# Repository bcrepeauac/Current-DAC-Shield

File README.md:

# Current-DAC-Shield
Current D-A Shield for Arduino

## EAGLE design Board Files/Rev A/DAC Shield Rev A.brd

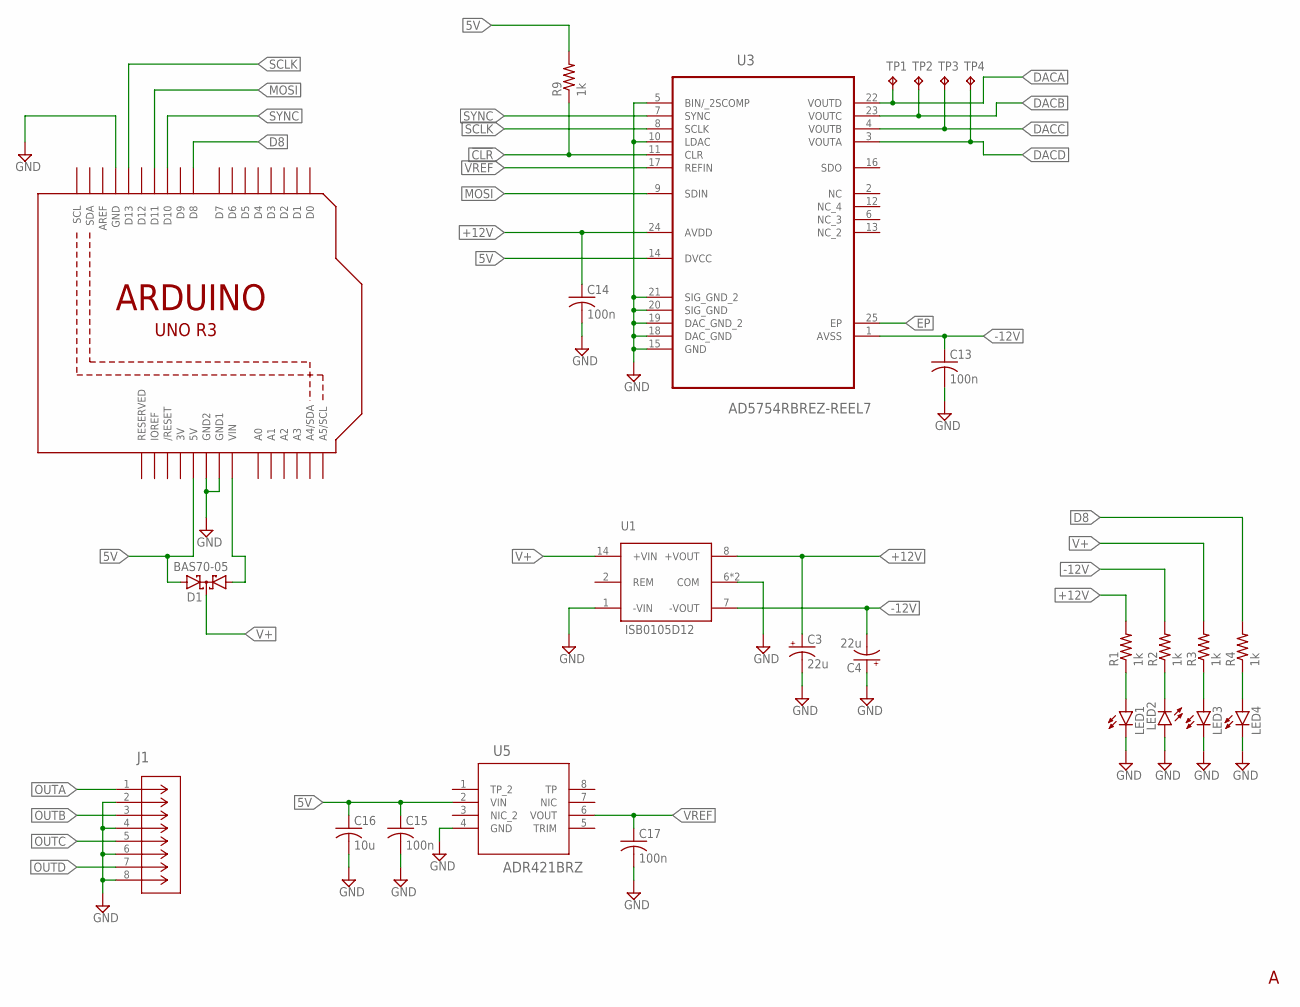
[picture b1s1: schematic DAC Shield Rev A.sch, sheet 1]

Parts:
C3, C4: 22u; C/6032-28W
C13, C14, C15, C17: 100n; C0805
C16: 10u; C0805
D1: BAS70-05; SOT23
J1: OSTVN08A150; CONN_OSTVN08A150_OST
LED1, LED2, LED3, LED4: LEDCHIPLED_0805; CHIPLED_0805
R1, R2, R3, R4, R9: 1k; R0805
TP1, TP2, TP3, TP4: TPB1,27; B1,27
U1: ISB0105D12; SOP254P1860X845-14L
U2: ARDUINOR3-BPLACE
U3: AD5754RBREZ-REEL7; SOP65P640X120-25N
U5: ADR421BRZ; R_8_ADI

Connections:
3V: U2.3V
5V: C15.1, C16.1, D1.2 (A2), R9.2, U2.5V, U3.14 (DVCC), U5.2 (VIN)
!CLR: R9.1, U3.11 (CLR)
+12V: C3.+, C14.1, R1.2, U1.8 (+VOUT), U3.24 (AVDD); also elsewhere on the board
-12V: C4.-, C13.1, R2.2, U1.7 (-VOUT), U3.1 (AVSS); also elsewhere on the board
D8: R4.2, U2.D8
DACA: TP1.TP, U3.22 (VOUTD); also elsewhere on the board
DACB: TP2.TP, U3.23 (VOUTC); also elsewhere on the board
DACC: TP3.TP, U3.4 (VOUTB); also elsewhere on the board
DACD: TP4.TP, U3.3 (VOUTA); also elsewhere on the board
EP: U3.25 (EP)
GND: C3.-, C4.+, C13.2, C14.2, C15.2, C16.2, C17.2, J1.2, J1.4, J1.6, J1.8, LED1.C, LED2.A, LED3.C, LED4.C, U1.1 (-VIN), U1.6 (COM), U1.9 (COM), U2.GND, U2.GND1, U2.GND2, U3.5 (BIN/_2SCOMP), U3.10 (LDAC), U3.15 (GND), U3.18 (DAC_GND), U3.19 (DAC_GND_2), U3.20 (SIG_GND), U3.21 (SIG_GND_2), U5.4 (GND); also elsewhere on the board
MOSI: U2.D11, U3.9 (SDIN)
unnamed: D1.1 (A1), U2.VIN
unnamed: LED1.A, R1.1
unnamed: LED2.C, R2.1
unnamed: LED3.A, R3.1
unnamed: LED4.A, R4.1
OUTA: J1.1; also elsewhere on the board
OUTB: J1.3; also elsewhere on the board
OUTC: J1.5; also elsewhere on the board
OUTD: J1.7; also elsewhere on the board
SCLK: U2.D13, U3.8 (SCLK)
SYNC: U2.D10, U3.7 (SYNC)
V+: D1.3 (C), R3.2, U1.14 (+VIN)
VREF: C17.1, U3.17 (REFIN), U5.6 (VOUT)

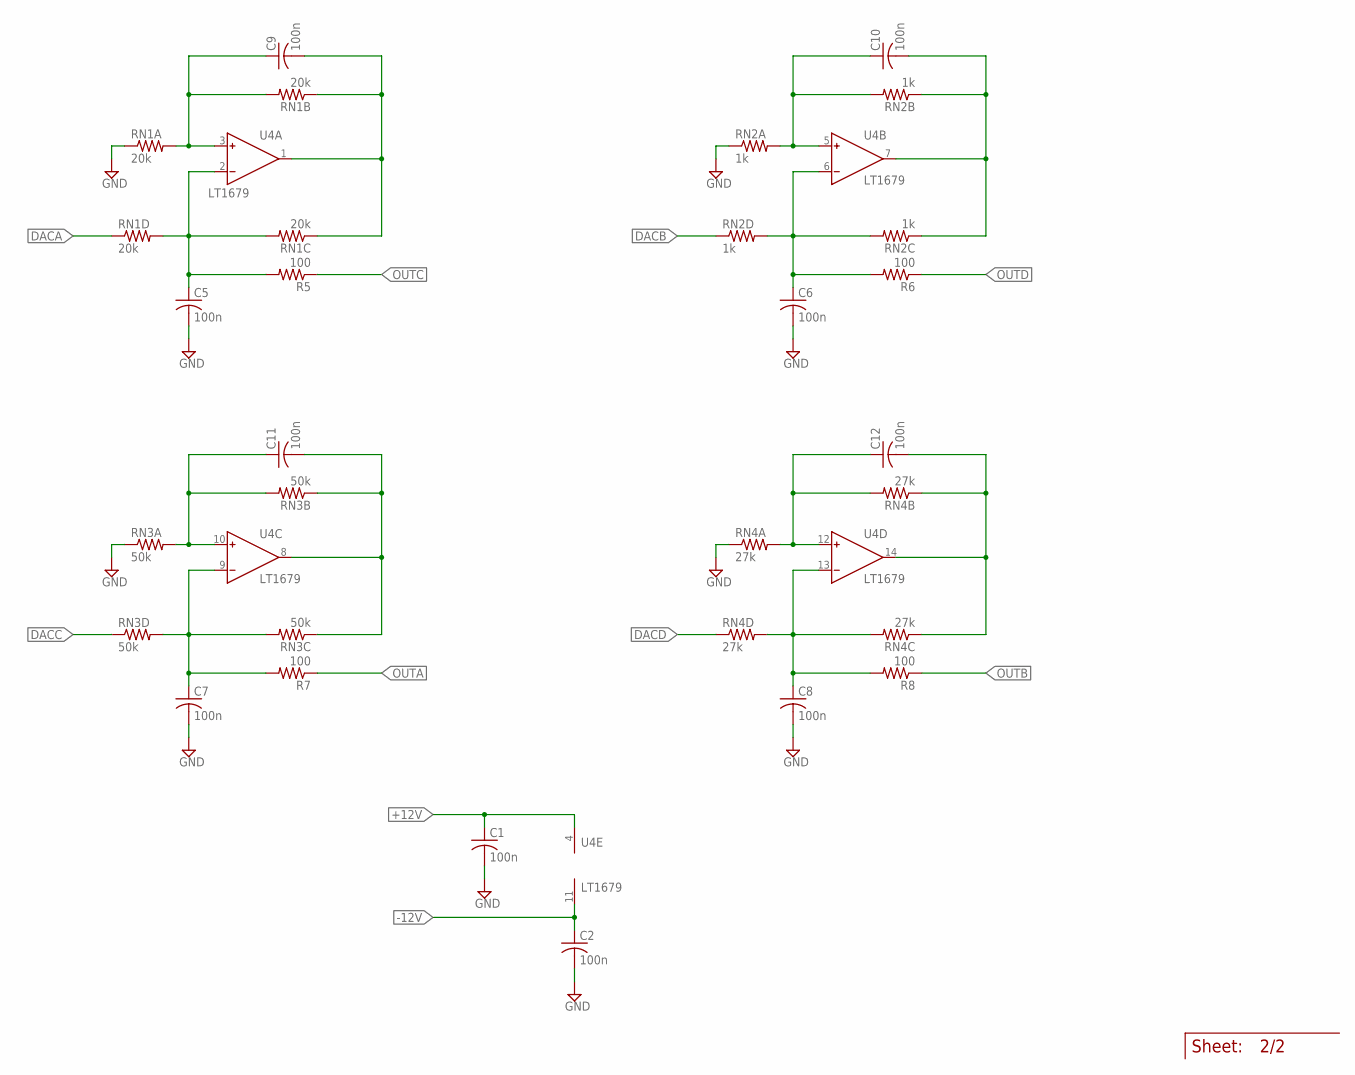
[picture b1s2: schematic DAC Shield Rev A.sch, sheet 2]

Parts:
C1, C2, C5, C6, C7, C8, C9, C10, C11, C12: 100n; C0805
R5, R6, R7, R8: 100; R0805
RN1: 20k; RESCAV80P320X150X55-8N
RN2: 1k; RESCAV80P320X150X55-8N
RN3: 50k; RESCAV80P320X150X55-8N
RN4: 27k; RESCAV80P320X150X55-8N
U4: LT1679; R_14_ADI-M

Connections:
+12V: C1.1, U4.4 (V+); also elsewhere on the board
-12V: C2.1, U4.11 (V-); also elsewhere on the board
DACA: RN1.4 (1); also elsewhere on the board
DACB: RN2.4 (1); also elsewhere on the board
DACC: RN3.4 (1); also elsewhere on the board
DACD: RN4.4 (1); also elsewhere on the board
GND: C1.2, C2.2, C5.2, C6.2, C7.2, C8.2, RN1.1, RN2.1, RN3.1, RN4.1; also elsewhere on the board
unnamed: C10.1, RN2.7 (2), RN2.8 (2), U4.5 (IN+)
unnamed: C9.1, RN1.7 (2), RN1.8 (2), U4.3 (IN+)
unnamed: C9.2, RN1.2 (1), RN1.3 (1), U4.1 (OUT)
unnamed: C10.2, RN2.2 (1), RN2.3 (1), U4.7 (OUT)
unnamed: C11.1, RN3.7 (2), RN3.8 (2), U4.10 (IN+)
unnamed: C11.2, RN3.2 (1), RN3.3 (1), U4.8 (OUT)
unnamed: C12.1, RN4.7 (2), RN4.8 (2), U4.12 (IN+)
unnamed: C12.2, RN4.2 (1), RN4.3 (1), U4.14 (OUT)
unnamed: C5.1, R5.2, RN1.5 (2), RN1.6 (2), U4.2 (IN-)
unnamed: C6.1, R6.2, RN2.5 (2), RN2.6 (2), U4.6 (IN-)
unnamed: C7.1, R7.2, RN3.5 (2), RN3.6 (2), U4.9 (IN-)
unnamed: C8.1, R8.2, RN4.5 (2), RN4.6 (2), U4.13 (IN-)
OUTA: R7.1; also elsewhere on the board
OUTB: R8.1; also elsewhere on the board
OUTC: R5.1; also elsewhere on the board
OUTD: R6.1; also elsewhere on the board

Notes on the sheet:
Sheet:

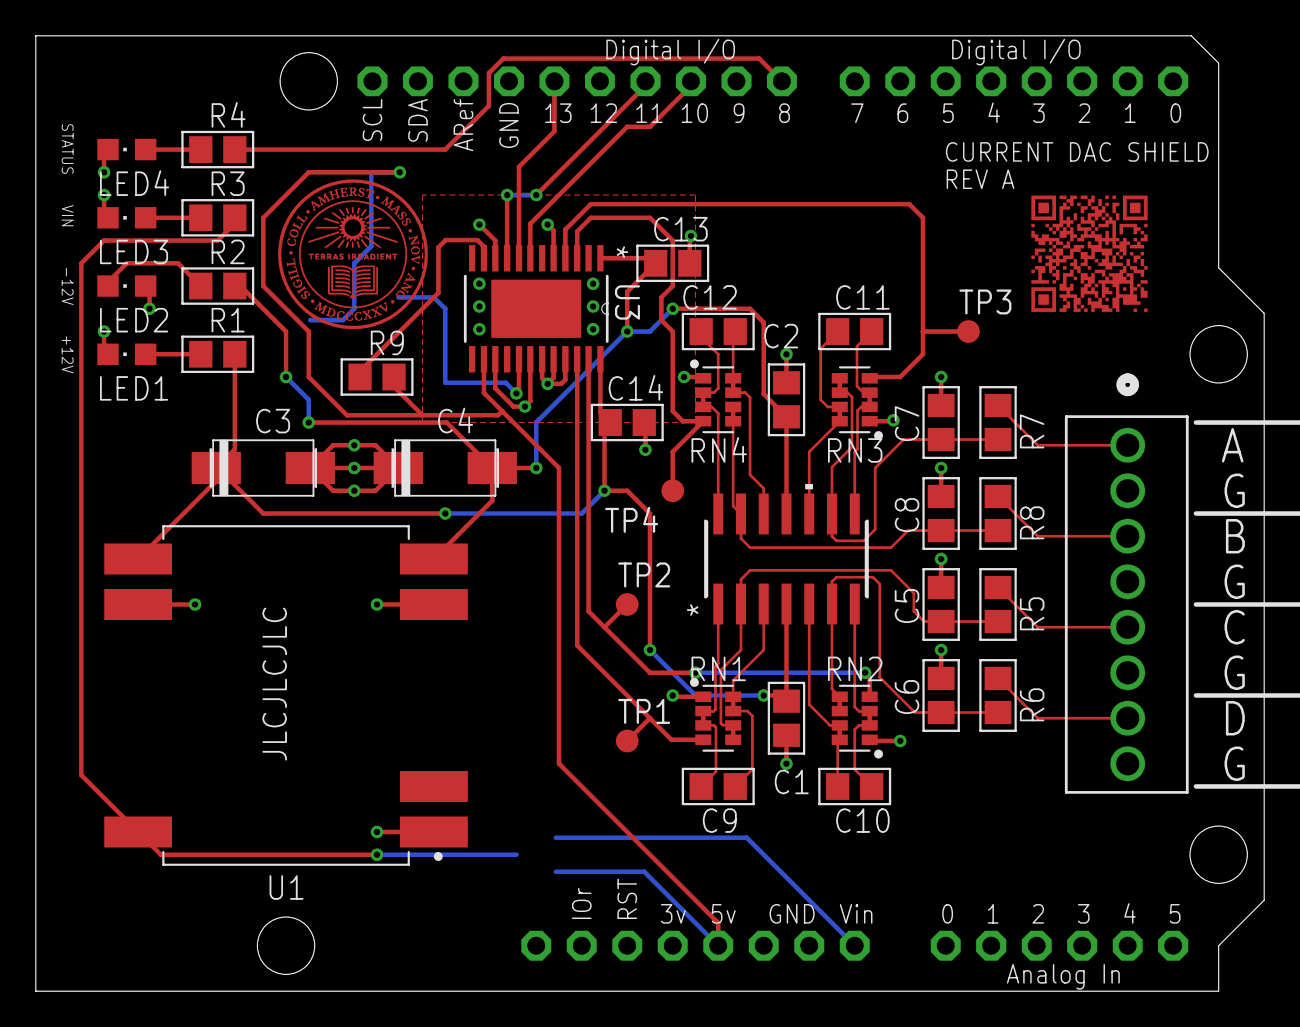
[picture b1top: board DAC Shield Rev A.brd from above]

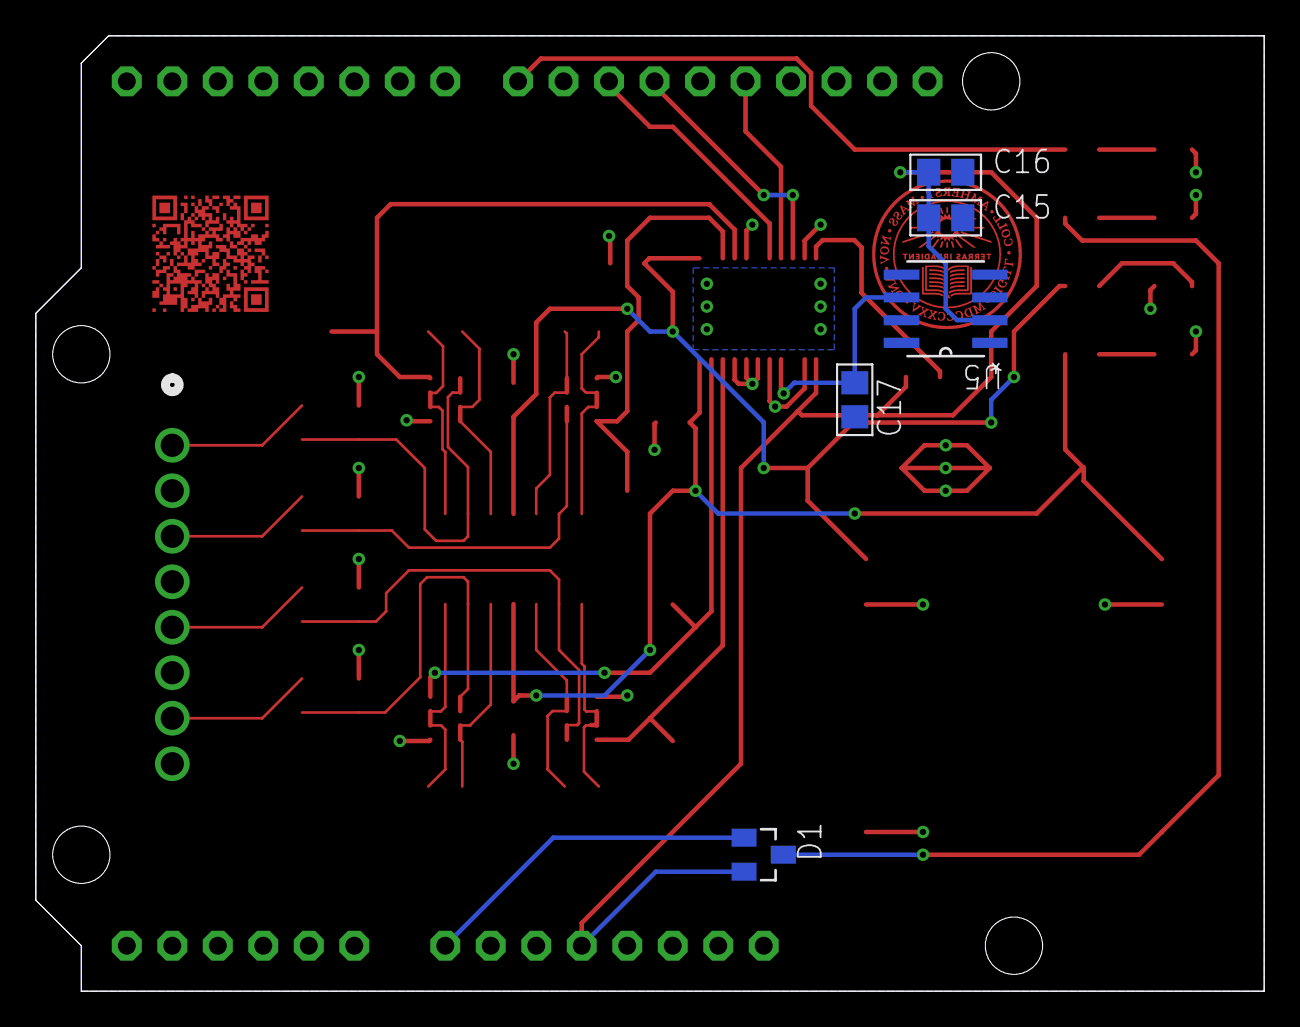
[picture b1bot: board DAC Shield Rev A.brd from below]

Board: 2 copper layers, 68.6 x 53.3 mm, 45 parts (5 on the bottom side), 36 nets.

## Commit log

2023-07-11 Added Set and Get functions
2023-07-12 Added SPI Code
2023-07-13 Added DAC
2023-07-13 Finished first draft of software
2023-08-29 Added rev B

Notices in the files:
parts and their libraries:
COPYRIGHT: Copyright (C) 2023 Ultra Librarian. All rights reserved.
